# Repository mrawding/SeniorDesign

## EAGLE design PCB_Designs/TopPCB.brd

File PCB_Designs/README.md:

This file contains schematics and PCB Designs for our modules

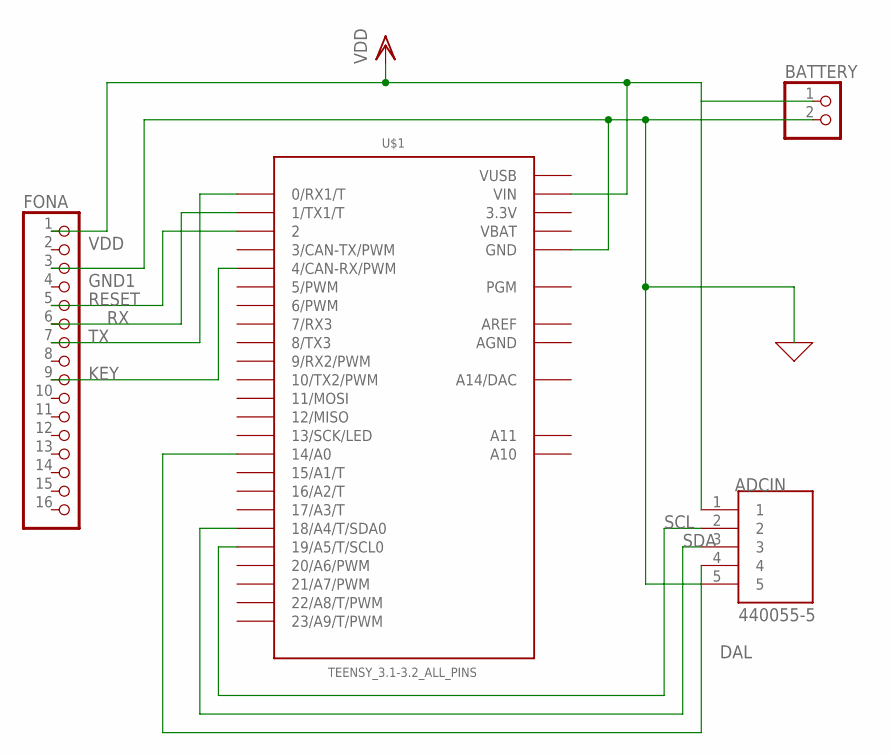
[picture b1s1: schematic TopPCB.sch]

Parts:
ADCIN: 440055-5; TE_440055-5
BATTERY: PINHD-1X2; 1X02
FONA: HEADER-1X16ROUND; 1X16_ROUND
U$1: TEENSY_3.1-3.2_ALL_PINS; TEENSY_3.0-3.2&LC_ALL_PINS

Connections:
3.3V: U$1.3.3V, U$1.3.3V1 (3.3V)
AGND: U$1.AGND
AREF: U$1.AREF
DAL: ADCIN.4, U$1.14/A0
GND1: ADCIN.5, BATTERY.2, FONA.3, U$1.GND, U$1.GND1 (GND)
KEY: FONA.9, U$1.4 (4/CAN-RX/PWM)
RESET: FONA.5, U$1.2
RX: FONA.6, U$1.1 (1/TX1/T)
SCL: ADCIN.2, U$1.19/A5 (19/A5/T/SCL0)
SDA: ADCIN.3, U$1.18/A4 (18/A4/T/SDA0)
TX: FONA.7, U$1.0 (0/RX1/T)
VBAT: U$1.VBAT
VDD: ADCIN.1, BATTERY.1, FONA.1, U$1.VIN
VUSB: U$1.VUSB

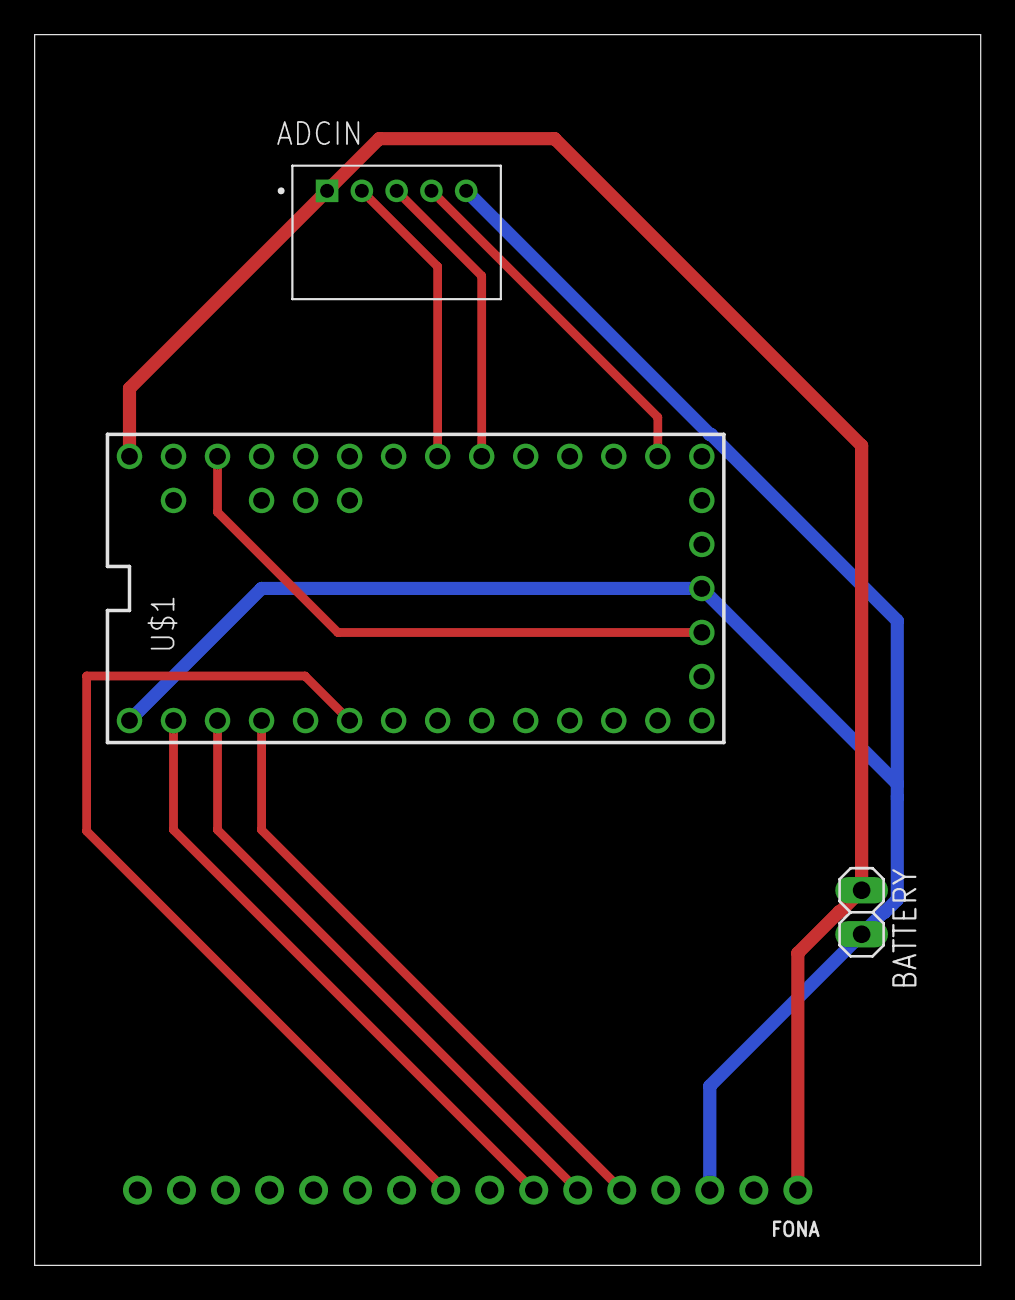
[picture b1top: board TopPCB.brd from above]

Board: 2 copper layers, 54.6 x 71.0 mm, 4 parts (0 on the bottom side), 10 nets.

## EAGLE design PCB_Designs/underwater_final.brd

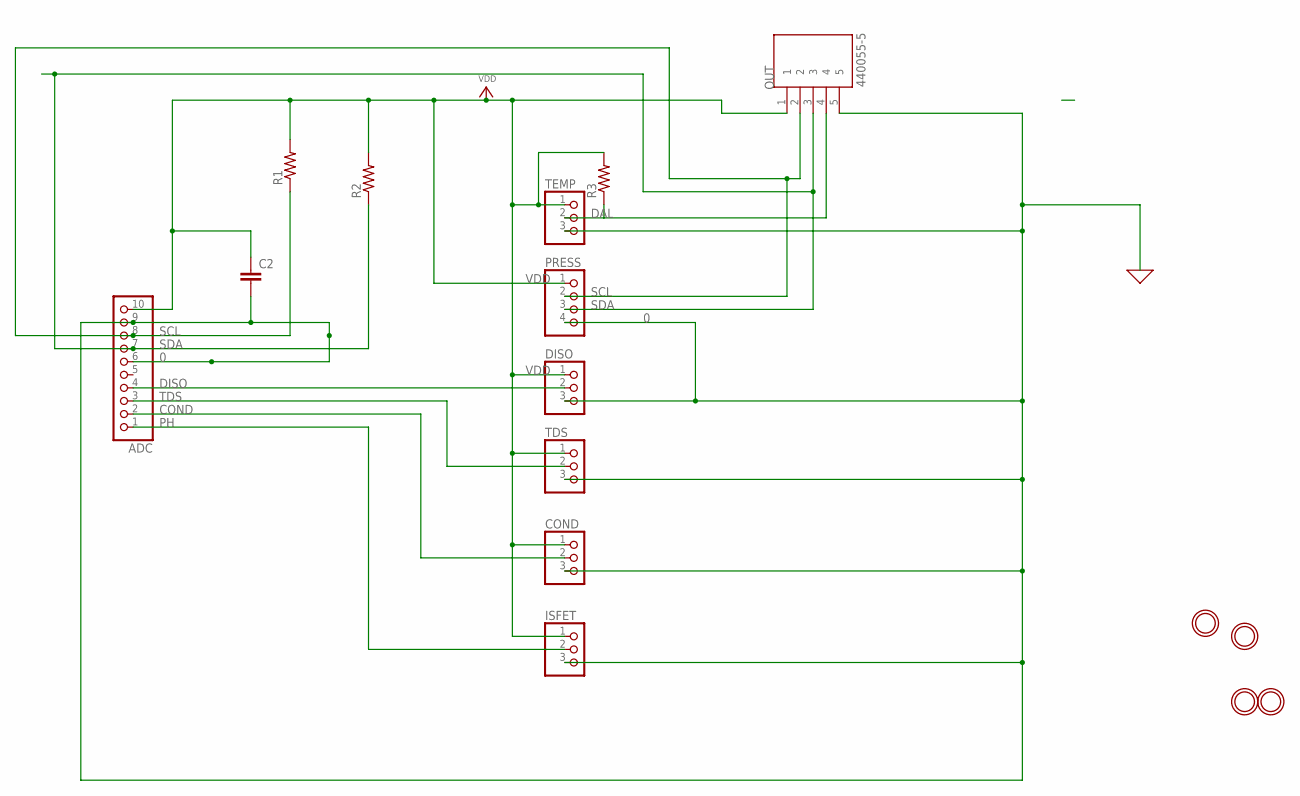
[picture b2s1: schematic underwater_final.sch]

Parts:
ADC: HEADER-1X1070MIL; 1X10_ROUND70
C2: C2.5/2; C2.5-2
COND: PINHD-1X3; 1X03
DISO: PINHD-1X3; 1X03
ISFET: PINHD-1X3; 1X03
OUT: 440055-5; TE_440055-5
PRESS: PINHD-1X4; 1X04
R1, R2, R3: R-US_0204/7; 0204/7
TDS: PINHD-1X3; 1X03
TEMP: PINHD-1X3; 1X03
U$2, U$3, U$13, U$14: MOUNTINGHOLE2.5; MOUNTINGHOLE_2.5_PLATED

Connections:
0: ADC.6, ADC.9, C2.2, COND.3, DISO.3, ISFET.3, OUT.5, PRESS.4, TDS.3, TEMP.3
COND: ADC.2, COND.2
DAL: OUT.4, R3.1, TEMP.2
DISO: ADC.4, DISO.2
PH: ADC.1, ISFET.2
SCL: ADC.8, OUT.2, PRESS.2, R1.1
SDA: ADC.7, OUT.3, PRESS.3, R2.1
TDS: ADC.3, TDS.2
VDD: ADC.10, C2.1, COND.1, DISO.1, ISFET.1, OUT.1, PRESS.1, R1.2, R2.2, R3.2, TDS.1, TEMP.1

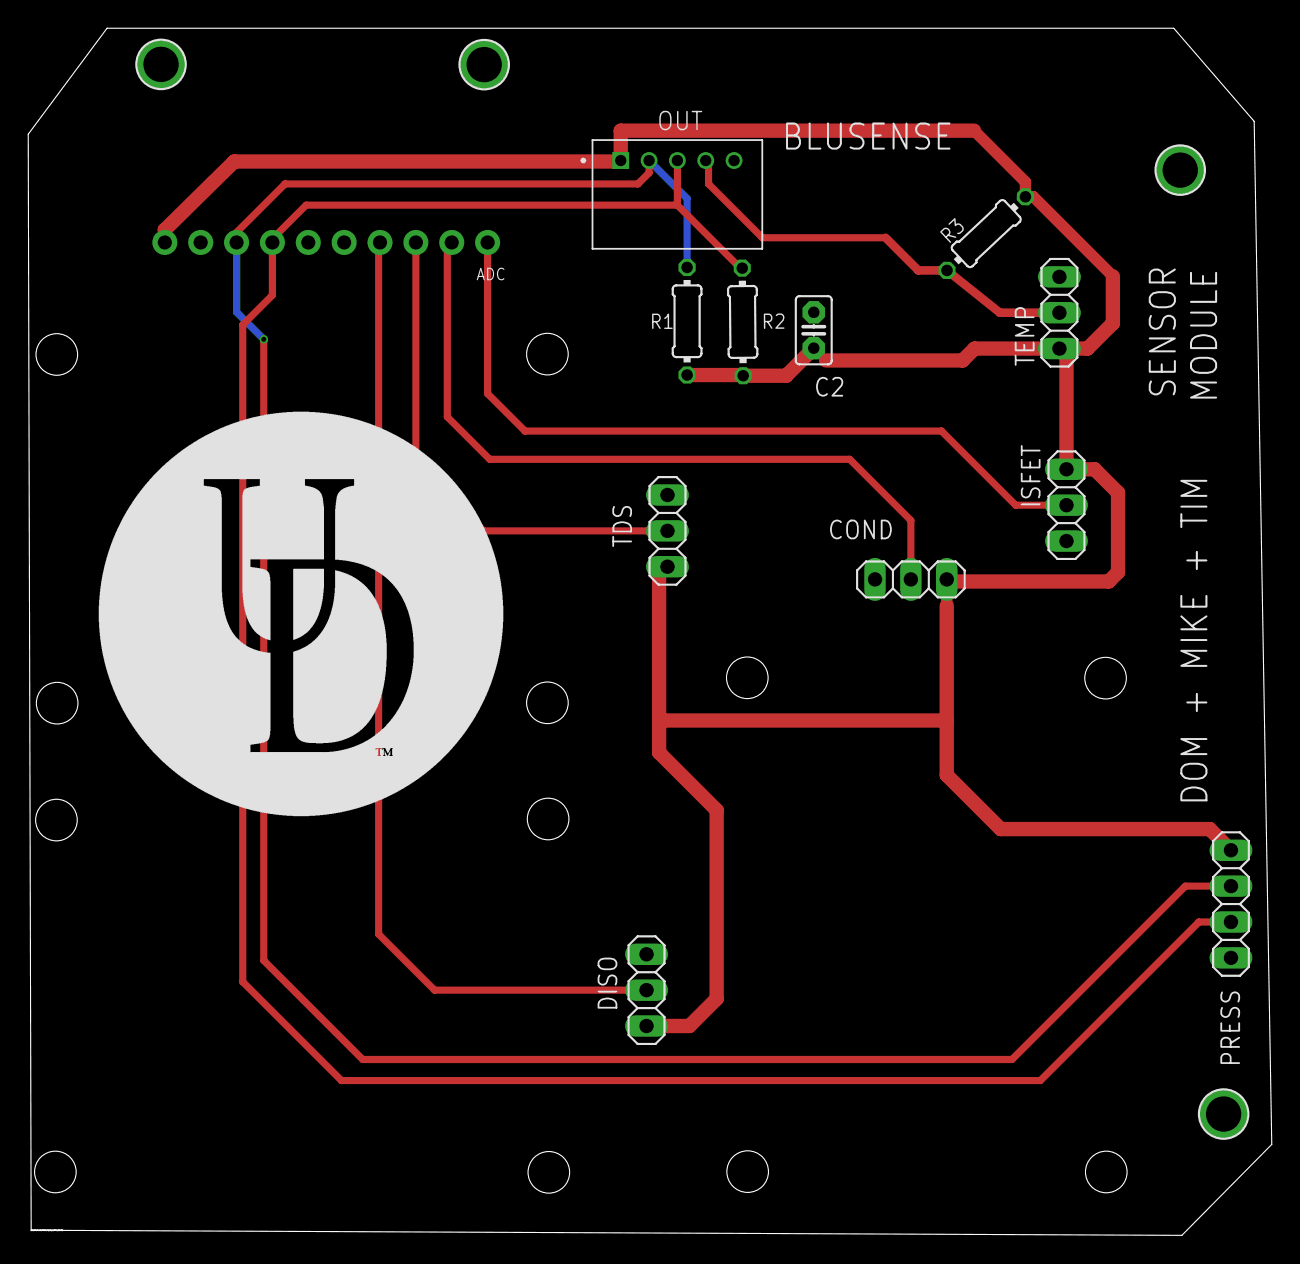
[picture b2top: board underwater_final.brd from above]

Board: 2 copper layers, 88.1 x 85.5 mm, 16 parts (0 on the bottom side), 9 nets.

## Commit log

2020-05-19 initial push
2020-05-19 Bump minimist from 1.2.0 to 1.2.5 in /blusenseAPI
    Bumps [minimist](https://github.com/substack/minimist) from 1.2.0 to 1.2.5.
    - [Release notes](https://github.com/substack/minimist/releases)
    - [Commits](https://github.com/substack/minimist/compare/1.2.0...1.2.5)
2020-05-19 created pcb folder
2020-05-21 final upload
2021-08-12 Bump path-parse from 1.0.6 to 1.0.7 in /blusenseAPI
    Bumps [path-parse](https://github.com/jbgutierrez/path-parse) from 1.0.6 to 1.0.7.
    - [Release notes](https://github.com/jbgutierrez/path-parse/releases)
    - [Commits](https://github.com/jbgutierrez/path-parse/commits/v1.0.7)
    ---
    updated-dependencies:
    - dependency-name: path-parse
2022-02-13 Bump ajv from 6.10.2 to 6.12.6 in /blusenseAPI
    Bumps [ajv](https://github.com/ajv-validator/ajv) from 6.10.2 to 6.12.6.
    - [Release notes](https://github.com/ajv-validator/ajv/releases)
    - [Commits](https://github.com/ajv-validator/ajv/compare/v6.10.2...v6.12.6)
    ---
    updated-dependencies:
    - dependency-name: ajv
2022-03-26 Bump minimist from 1.2.0 to 1.2.6 in /blusenseAPI
    Bumps [minimist](https://github.com/substack/minimist) from 1.2.0 to 1.2.6.
    - [Release notes](https://github.com/substack/minimist/releases)
    - [Commits](https://github.com/substack/minimist/compare/1.2.0...1.2.6)
    ---
    updated-dependencies:
    - dependency-name: minimist
2022-12-07 Bump qs from 6.5.2 to 6.5.3 in /blusenseAPI
    Bumps [qs](https://github.com/ljharb/qs) from 6.5.2 to 6.5.3.
    - [Release notes](https://github.com/ljharb/qs/releases)
    - [Changelog](https://github.com/ljharb/qs/blob/main/CHANGELOG.md)
    - [Commits](https://github.com/ljharb/qs/compare/v6.5.2...v6.5.3)
    ---
    updated-dependencies:
2022-12-12 Bump express from 4.17.1 to 4.17.3 in /blusenseAPI
    Bumps [express](https://github.com/expressjs/express) from 4.17.1 to 4.17.3.
    - [Release notes](https://github.com/expressjs/express/releases)
    - [Changelog](https://github.com/expressjs/express/blob/master/History.md)
    - [Commits](https://github.com/expressjs/express/compare/4.17.1...4.17.3)
    ---
    updated-dependencies:

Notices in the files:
parts and their libraries:
microbuilder: This work is placed in the public domain, and may be freely used for commercial and non-commercial work with the following conditions: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
